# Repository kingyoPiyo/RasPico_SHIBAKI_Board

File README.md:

# RasPico_SHIBAKI_Board
Raspberry Pi Pico で色々やる基板です。  

### 搭載インタフェース
| インタフェース | 説明 |
| ---- | ---- |
| SFP | 2スロット搭載。TXRX、LOS、TX_FAULT、I2C の基本的な信号線が Pico と接続されています。RATE_SELECT、TX_DISABLE ははんだジャンパで指定します。 |
| GPIO | 2.54mm pitch 2x5ピンヘッダを搭載。4pin + 3.3V + GND が出ています。機能拡張等に使用できます。 |
| LED | 4個搭載（Pico ボードに標準搭載のLEDを含めると合計5個）。Lチカデバッグや UART、S/PDIF 信号を出力して遊べます。 |
| Push SW | User 用2個（プルアップ抵抗付き）、Reset 用1個搭載 |
| SMA Input | 2個搭載。50Ω終端抵抗（標準では未実装）を実装するパッドを用意しています。 |
| SMA Output | 2個搭載。標準で 450Ω の抵抗が直列に挿入されています。50Ω 終端可能なオシロスコープに接続するとx10減衰として機能します。レベルを変更したい場合は適宜抵抗を打ち替えてください。 |

### 基板画像

## サンプルソフトウェア
本ボードで遊べるサンプルプログラムです。  
100BASE-FX による UDP 送信例、VBAN プロトコルによる PCM データ送信、SFP モジュール情報読み出し、8b10b エンコード・デコード（PIO を使った SerDes with Clockrecovery）等を追々追加していく予定です。  
| Link | 説明 |
| ---- | ---- |
| [hwtest](firmware/hwtest/ "hwtest") | ハードウェアテスト用。<br> リセット直後にUSBシリアルから各ピンの電圧レベルやSFPモジュールのI2C読み出しデータ（Addr 0x50）等が出力されます。SW0押下でSFP0ポートからUDPパケットを100BASE-FXでブロードキャストします。SFP1の送受信は実装中... |
| [vban](firmware/vban/ "vban") | RasPico ADC + VBAN Protocol サンプル。<br> GP26(ADC0), GP27(ADC1) からオーディオ信号を入力すると、方チャンネル44.1kHzでサンプリングされてVBANプロトコルに載せてストリーミング送信します。ネットワーク設定はudp.hを適宜書き換えてください。 |
| [pattern_gen](firmware/pattern_gen/ "pattern_gen") | PIOを活用したパターンジェネレータサンプル。<br> SFP0とSMAOUT0端子から125MS/sで位相同期した任意のパターンを出力します。<br> SFPモジュールの伝搬遅延の評価等に使えます。サンプリングクロック周波数や出力端子も任意に設定可能です。 |

## 回路図
[Schematic.pdf](doc/schematic.pdf "Schematic")

## 既知のバグ
[doc/Rev1.0_Jumper.png](doc/Rev1.0_Jumper.png "Rev1.0_Jumper.png") 参照
* SFP0_SCLとSFP0_SDAのピンアサインを入れ替える必要あり
* SFP1_SCLがI2C1_SCLに、SFP1_SDAがI2C0_SDAに割りあたっており、配線修正必要

## 開発環境
- KiCad Version 6.0.5
- Raspberry Pi Pico 3D model and Footprint : [KiCad-RP-Pico](https://github.com/ncarandini/KiCad-RP-Pico "KiCad-RP-Pico")

## pico-sdk install memo
```
sudo apt install cmake gcc-arm-none-eabi libnewlib-arm-none-eabi libstdc++-arm-none-eabi-newlib build-essential
git clone https://github.com/raspberrypi/pico-sdk
cd pico-sdk
git submodule update --init
```

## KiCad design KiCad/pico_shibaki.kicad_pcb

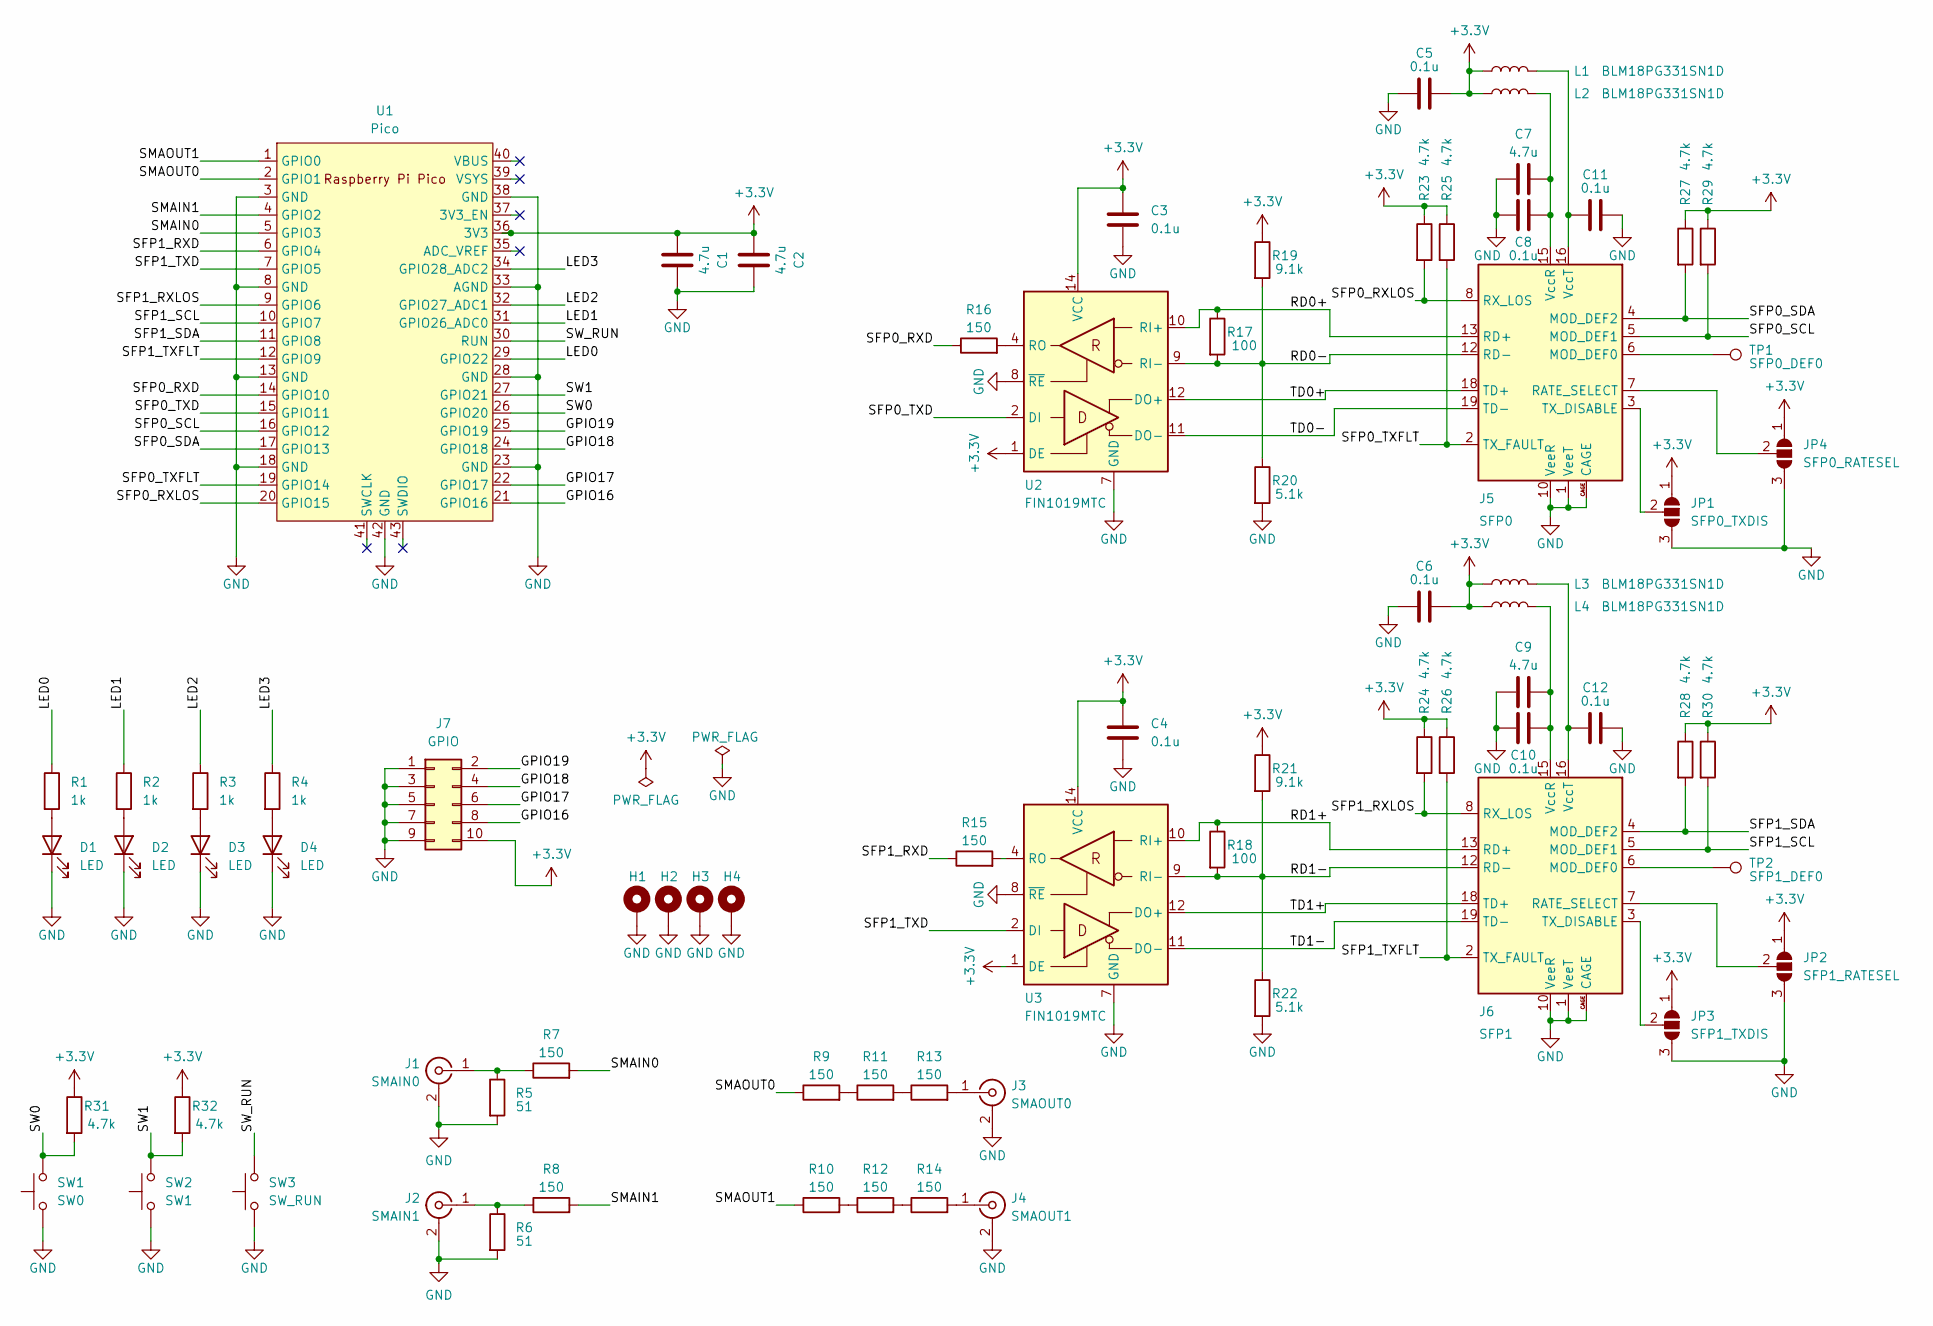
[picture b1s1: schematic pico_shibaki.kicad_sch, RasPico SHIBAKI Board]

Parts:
C1, C2, C7, C9: 4.7u; C_0603_1608Metric
C3, C4, C5, C6, C8, C10, C11, C12: 0.1u; C_0402_1005Metric
D1, D2, D3, D4: LED; LED_0603_1608Metric
H1, H2, H3, H4: MountingHole_Pad; MountingHole_3.2mm_M3_Pad_Via
J1: SMAIN0; SMA_Amphenol_132134_Vertical
J2: SMAIN1; SMA_Amphenol_132134_Vertical
J3: SMAOUT0; SMA_Amphenol_132134_Vertical
J4: SMAOUT1; SMA_Amphenol_132134_Vertical
J5: SFP0; Connector_SFP_and_Cage
J6: SFP1; Connector_SFP_and_Cage
J7: GPIO; PinHeader_2x05_P2.54mm_Vertical
JP1: SFP0_TXDIS; SolderJumper-3_P1.3mm_Open_RoundedPad1.0x1.5mm_NumberLabels
JP2: SFP1_RATESEL; SolderJumper-3_P1.3mm_Open_RoundedPad1.0x1.5mm_NumberLabels
JP3: SFP1_TXDIS; SolderJumper-3_P1.3mm_Open_RoundedPad1.0x1.5mm_NumberLabels
JP4: SFP0_RATESEL; SolderJumper-3_P1.3mm_Open_RoundedPad1.0x1.5mm_NumberLabels
L1, L2, L3, L4: BLM18PG331SN1D; L_0603_1608Metric
R1, R2, R3, R4: 1k; R_0603_1608Metric
R5, R6: 51; R_0603_1608Metric
R7, R8, R9, R10, R11, R12, R13, R14, R15, R16: 150; R_0402_1005Metric
R17, R18: 100; R_0402_1005Metric
R19, R21: 9.1k; R_0402_1005Metric
R20, R22: 5.1k; R_0402_1005Metric
R23, R24, R25, R26, R27, R28, R29, R30, R31, R32: 4.7k; R_0402_1005Metric
SW1: SW0; SW_Push_1P1T_NO_Vertical_Wuerth_434133025816
SW2: SW1; SW_Push_1P1T_NO_Vertical_Wuerth_434133025816
SW3: SW_RUN; SW_Push_1P1T_NO_Vertical_Wuerth_434133025816
TP1: SFP0_DEF0; TestPoint_Pad_D1.0mm
TP2: SFP1_DEF0; TestPoint_Pad_D1.0mm
U1: Pico; RPi_Pico_SMD_TH
U2, U3: FIN1019MTC; TSSOP-14_4.4x5mm_P0.65mm

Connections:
+3V3: C1.1, C2.1, C3.1, C4.1, C5.2, C6.2, J7.10, JP1.1 (A), JP2.1 (A), JP3.1 (A), JP4.1 (A), L1.1, L2.1, L3.1, L4.1, R19.1, R21.1, R23.1, R24.1, R25.1, R26.1, R27.1, R28.1, R29.1, R30.1, R31.1, R32.1, U1.36 (3V3), U2.1 (DE), U2.14 (VCC), U3.1 (DE), U3.14 (VCC)
/GPIO16: J7.8, U1.21 (GPIO16)
/GPIO17: J7.6, U1.22 (GPIO17)
/GPIO18: J7.4, U1.24 (GPIO18)
/GPIO19: J7.2, U1.25 (GPIO19)
/LED0: R1.1, U1.29 (GPIO22)
/LED1: R2.1, U1.31 (GPIO26_ADC0)
/LED2: R3.1, U1.32 (GPIO27_ADC1)
/LED3: R4.1, U1.34 (GPIO28_ADC2)
/RD0+: J5.13 (RD+), R17.1, U2.10 (RI+)
/RD0-: J5.12 (RD-), R17.2, R19.2, R20.1, U2.9 (RI-)
/RD1+: J6.13 (RD+), R18.1, U3.10 (RI+)
/RD1-: J6.12 (RD-), R18.2, R21.2, R22.1, U3.9 (RI-)
/SFP0_RXD: R16.1, U1.14 (GPIO10)
/SFP0_RXLOS: J5.8 (RX_LOS), R23.2, U1.20 (GPIO15)
/SFP0_SCL: J5.5 (MOD_DEF1), R29.2, U1.16 (GPIO12)
/SFP0_SDA: J5.4 (MOD_DEF2), R27.2, U1.17 (GPIO13)
/SFP0_TXD: U1.15 (GPIO11), U2.2 (DI)
/SFP0_TXFLT: J5.2 (TX_FAULT), R25.2, U1.19 (GPIO14)
/SFP1_RXD: R15.1, U1.6 (GPIO4)
/SFP1_RXLOS: J6.8 (RX_LOS), R24.2, U1.9 (GPIO6)
/SFP1_SCL: J6.5 (MOD_DEF1), R30.2, U1.10 (GPIO7)
/SFP1_SDA: J6.4 (MOD_DEF2), R28.2, U1.11 (GPIO8)
/SFP1_TXD: U1.7 (GPIO5), U3.2 (DI)
/SFP1_TXFLT: J6.2 (TX_FAULT), R26.2, U1.12 (GPIO9)
/SMAIN0: R7.2, U1.5 (GPIO3)
/SMAIN1: R8.2, U1.4 (GPIO2)
/SMAOUT0: R9.1, U1.2 (GPIO1)
/SMAOUT1: R10.1, U1.1 (GPIO0)
/SW0: R31.2, SW1.2, U1.26 (GPIO20)
/SW1: R32.2, SW2.2, U1.27 (GPIO21)
/SW_RUN: SW3.2, U1.30 (RUN)
/TD0+: J5.18 (TD+), U2.12 (DO+)
/TD0-: J5.19 (TD-), U2.11 (DO-)
/TD1+: J6.18 (TD+), U3.12 (DO+)
/TD1-: J6.19 (TD-), U3.11 (DO-)
GND: C1.2, C2.2, C3.2, C4.2, C5.1, C6.1, C7.1, C8.1, C9.1, C10.1, C11.2, C12.2, D1.1 (K), D2.1 (K), D3.1 (K), D4.1 (K), H1.1, H2.1, H3.1, H4.1, J1.2 (Ext), J2.2 (Ext), J3.2 (Ext), J4.2 (Ext), J5.1 (VeeT), J5.9 (VeeR), J5.10 (VeeR), J5.11 (VeeR), J5.14 (VeeR), J5.17 (VeeT), J5.20 (VeeT), J5.CAGE, J6.1 (VeeT), J6.9 (VeeR), J6.10 (VeeR), J6.11 (VeeR), J6.14 (VeeR), J6.17 (VeeT), J6.20 (VeeT), J6.CAGE, J7.1, J7.3, J7.5, J7.7, J7.9, JP1.3 (B), JP2.3 (B), JP3.3 (B), JP4.3 (B), R5.2, R6.2, R20.2, R22.2, SW1.1, SW2.1, SW3.1, U1.3 (GND), U1.8 (GND), U1.13 (GND), U1.18 (GND), U1.23 (GND), U1.28 (GND), U1.33 (AGND), U1.38 (GND), U1.42 (GND), U2.7 (GND), U2.8 (~RE), U3.7 (GND), U3.8 (~RE)
unnamed: C7.2, C8.2, J5.15 (VccR), L2.2
unnamed: C9.2, C10.2, J6.15 (VccR), L4.2
unnamed: C11.1, J5.16 (VccT), L1.2
unnamed: C12.1, J6.16 (VccT), L3.2
unnamed: D1.2 (A), R1.2
unnamed: D2.2 (A), R2.2
unnamed: D3.2 (A), R3.2
unnamed: D4.2 (A), R4.2
unnamed: J1.1 (In), R5.1, R7.1
unnamed: J2.1 (In), R6.1, R8.1
unnamed: J3.1 (In), R13.2
unnamed: J4.1 (In), R14.2
unnamed: J5.3 (TX_DISABLE), JP1.2 (C)
unnamed: J5.6 (MOD_DEF0), TP1.1
unnamed: J5.7 (RATE_SELECT), JP4.2 (C)
unnamed: J6.3 (TX_DISABLE), JP3.2 (C)
unnamed: J6.6 (MOD_DEF0), TP2.1
unnamed: J6.7 (RATE_SELECT), JP2.2 (C)
unnamed: R10.2, R12.1
unnamed: R9.2, R11.1
unnamed: R11.2, R13.1
unnamed: R12.2, R14.1
unnamed: R15.2, U3.4 (RO)
unnamed: R16.2, U2.4 (RO)

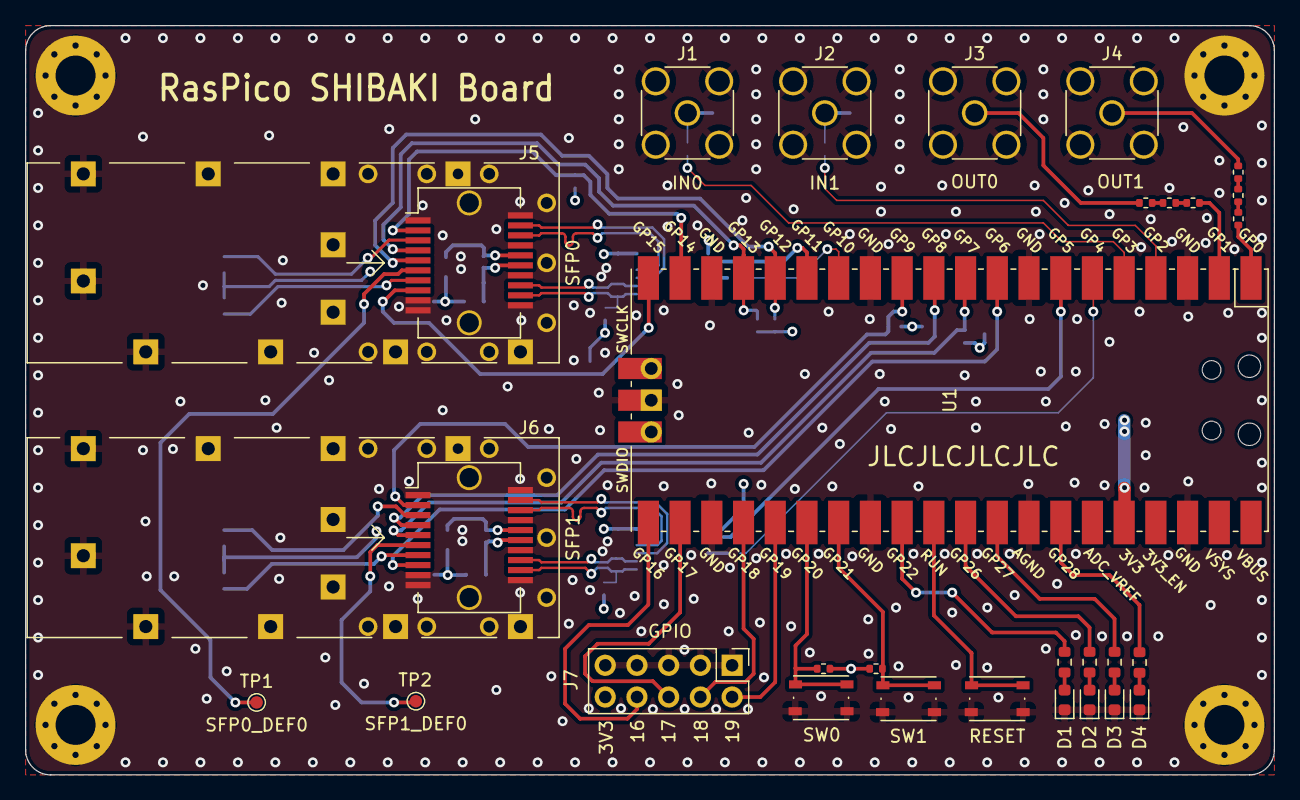
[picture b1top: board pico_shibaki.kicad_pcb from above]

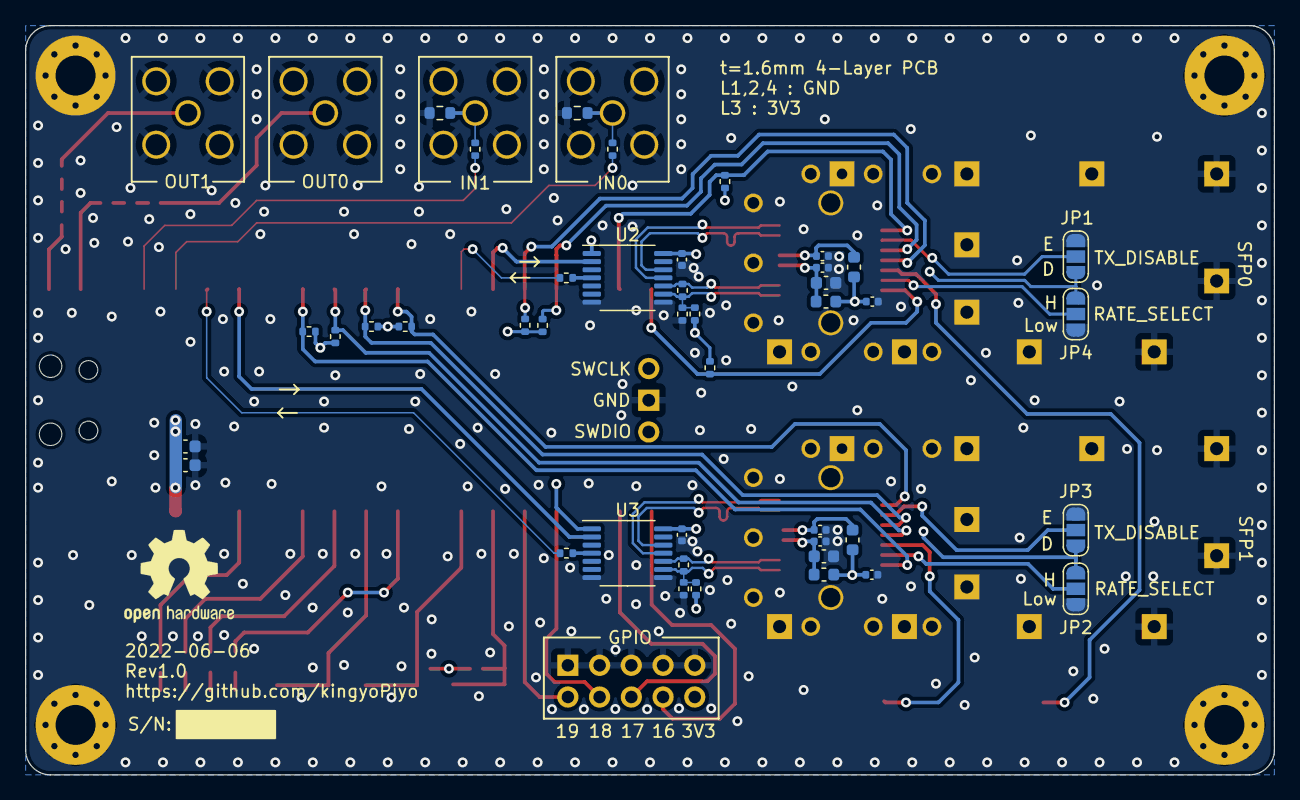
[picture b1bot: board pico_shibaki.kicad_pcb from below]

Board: 4 copper layers, 100.0 x 60.0 mm, 75 parts (42 on the bottom side), 61 nets.

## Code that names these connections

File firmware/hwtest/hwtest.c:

#include "hwtest.h"
#include "pico/stdlib.h"
#include <stdio.h>
#include <stdint.h>
#include "hw.h"
#include "hardware/i2c.h"


static struct repeating_timer timer;

// Timer interrupt (L-tika)
static bool repeating_timer_callback(struct repeating_timer *t)
{
    static bool led0_state = true;

    gpio_put(HW_PINNUM_LED0, led0_state);
    led0_state = !led0_state;

    // true to continue repeating, false to stop.
    return true;
}

// Read SFP I2C EEPROM, Address = 0x50
static void read_i2c_data(i2c_inst_t *i2c)
{
    uint8_t read_buf[256] = {0};
    uint32_t x = 0, y = 0;
    uint8_t tmp;

    i2c_read_blocking(i2c, 0x50, read_buf, 256, false);

    printf(" 0x50 0  1  2  3  4  5  6  7  8  9  a  b  c  d  e  f    0123456789abcdef\r\n");
    for (y = 0; y < 16; y++) {
        printf(" %02x: ", y << 4);
        for (x = 0; x < 16; x++) {
            printf("%02x ", read_buf[(y << 4) + x]);
        }
        printf("   ");
        for (x = 0; x < 16; x++) {
            tmp = read_buf[(y << 4) + x];
            if (tmp >= 0x20 && tmp <= 0x7E) {
                printf("%c", tmp);
            } else {
                printf(".");
            }
        }
        printf("\r\n");
    }
}

// Read GPIO Level
static void uart_debug_output(void)
{
    uint32_t io_status_now;
    static uint32_t io_status_old = 0xFFFFFFFF;

    // I/O sampling
    io_status_now = 0;
    io_status_now |= gpio_get(HW_PINNUM_SFP0_TXFLT) ? 1 << 0 : 0;
    io_status_now |= gpio_get(HW_PINNUM_SFP0_RXLOS) ? 1 << 1 : 0;
    io_status_now |= gpio_get(HW_PINNUM_SFP0_SCL)   ? 1 << 2 : 0;
    io_status_now |= gpio_get(HW_PINNUM_SFP0_SDA)   ? 1 << 3 : 0;
    io_status_now |= gpio_get(HW_PINNUM_SFP1_TXFLT) ? 1 << 4 : 0;
    io_status_now |= gpio_get(HW_PINNUM_SFP1_RXLOS) ? 1 << 5 : 0;
    io_status_now |= gpio_get(HW_PINNUM_SFP1_SCL)   ? 1 << 6 : 0;
    io_status_now |= gpio_get(HW_PINNUM_SFP1_SDA)   ? 1 << 7 : 0;
    io_status_now |= gpio_get(HW_PINNUM_SMAIN0)     ? 1 << 8 : 0;
    io_status_now |= gpio_get(HW_PINNUM_SMAIN1)     ? 1 << 9 : 0;
    io_status_now |= gpio_get(HW_PINNUM_SW0)        ? 1 << 10 : 0;
    io_status_now |= gpio_get(HW_PINNUM_SW1)        ? 1 << 11 : 0;
    io_status_now |= gpio_get(HW_PINNUM_GPIO16)     ? 1 << 12 : 0;
    io_status_now |= gpio_get(HW_PINNUM_GPIO17)     ? 1 << 13 : 0;
    io_status_now |= gpio_get(HW_PINNUM_GPIO18)     ? 1 << 14 : 0;
    io_status_now |= gpio_get(HW_PINNUM_GPIO19)     ? 1 << 15 : 0;

    if (io_status_now != io_status_old)
    {
        printf("\033[H\033[2J");
        printf("## RasPico SHIBAKI Board  Demo firmware ##\r\n");

        // SFP Status
        printf("SFP0\r\n");
        io_status_now & (1 << 0)    ? printf(" TXFLT   : High\r\n") : printf(" TXFLT   : Low\r\n");
        io_status_now & (1 << 1)    ? printf(" RXLOS   : High\r\n") : printf(" RXLOS   : Low\r\n");
        io_status_now & (1 << 2)    ? printf(" SCL     : High\r\n") : printf(" SCL     : Low\r\n");
        io_status_now & (1 << 3)    ? printf(" SDA     : High\r\n") : printf(" SDA     : Low\r\n");
        read_i2c_data(i2c0);
        printf("SFP1\r\n");
        io_status_now & (1 << 4)    ? printf(" TXFLT   : High\r\n") : printf(" TXFLT   : Low\r\n");
        io_status_now & (1 << 5)    ? printf(" RXLOS   : High\r\n") : printf(" RXLOS   : Low\r\n");
        io_status_now & (1 << 6)    ? printf(" SCL     : High\r\n") : printf(" SCL     : Low\r\n");
        io_status_now & (1 << 7)    ? printf(" SDA     : High\r\n") : printf(" SDA     : Low\r\n");
        read_i2c_data(i2c1);
        // SMA Input Status
        io_status_now & (1 << 8)    ? printf("SMA_IN0  : High\r\n") : printf("SMA_IN0  : Low\r\n");
        io_status_now & (1 << 9)    ? printf("SMA_IN1  : High\r\n") : printf("SMA_IN1  : Low\r\n");
        // User SW Status
        io_status_now & (1 << 10)   ? printf("SW0      : High\r\n") : printf("SW0      : Low\r\n");
        io_status_now & (1 << 11)   ? printf("SW1      : High\r\n") : printf("SW1      : Low\r\n");
        // GPIO Level
        io_status_now & (1 << 12)   ? printf("GPIO16   : High\r\n") : printf("GPIO16   : Low\r\n");
        io_status_now & (1 << 13)   ? printf("GPIO17   : High\r\n") : printf("GPIO17   : Low\r\n");
        io_status_now & (1 << 14)   ? printf("GPIO18   : High\r\n") : printf("GPIO18   : Low\r\n");
        io_status_now & (1 << 15)   ? printf("GPIO19   : High\r\n") : printf("GPIO19   : Low\r\n");

        io_status_old = io_status_now;
        sleep_ms(20);
    }
}

// HW test
void hw_test(void)
{
    bool uart_loop_forever = false;

    // If SW0 pushed, uart debug message forever..
    if (!gpio_get(HW_PINNUM_SW0)) {
        uart_loop_forever = true;
    } else {
        uart_loop_forever = false;
    }

    // ALL LED ON
    gpio_put(HW_PINNUM_LED0, true);
    gpio_put(HW_PINNUM_LED1, true);
    gpio_put(HW_PINNUM_LED2, true);
    gpio_put(HW_PINNUM_LED3, true);
    gpio_put(HW_PINNUM_LED4, true);
    sleep_ms(1000);
    // ALL LED OFF
    gpio_put(HW_PINNUM_LED4, false);
    sleep_ms(150);
    gpio_put(HW_PINNUM_LED3, false);
    sleep_ms(150);
    gpio_put(HW_PINNUM_LED2, false);
    sleep_ms(150);
    gpio_put(HW_PINNUM_LED1, false);
    sleep_ms(150);
    gpio_put(HW_PINNUM_LED0, false);

    do {
        uart_debug_output();
    } while (uart_loop_forever);

    // Timer interrupt
    add_repeating_timer_ms(-500, repeating_timer_callback, NULL, &timer);

    sleep_ms(1000);
}

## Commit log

2022-06-05 Add some files
2022-06-05 update..
2022-06-05 Add KiCad project files
2022-07-03 Add hwtest code
2022-07-11 Add SHIBAKIs Picture.
2022-07-12 Add gitignore
2022-07-12 fixed unko
2022-07-12 oyo~
2022-07-12 Add UART debug message "forever mode"
2022-07-13 i2c pinout bug....
2022-07-13 Add SFP I2C EEPROM Read
2022-07-13 Add Rev1.0 Jumper point
2022-07-19 Add Pico onboard LED!!
2022-07-21 Accurate time.
2022-07-24 Add VBAN Sample.
2022-07-24 Add pic..
2022-07-25 DCDC is PWM mode....
2022-07-25 x4 Oversampling!!
2022-07-26 Improved stability....?
2022-08-04 4b -> 8b
2022-08-04 Placed in RAM
2022-08-07 Improved UDP packet gen
2023-01-05 Accelerated using DMA
2023-12-28 Add Pattern Generator sample.
2023-12-28 動作表示追加
2023-12-28 Warning対策
2023-12-28 プロジェクト名変更&RAM展開有効化
2023-12-28 プロジェクト名変更
2023-12-28 Add udp_test
2024-08-16 Add include file : clocks.h
